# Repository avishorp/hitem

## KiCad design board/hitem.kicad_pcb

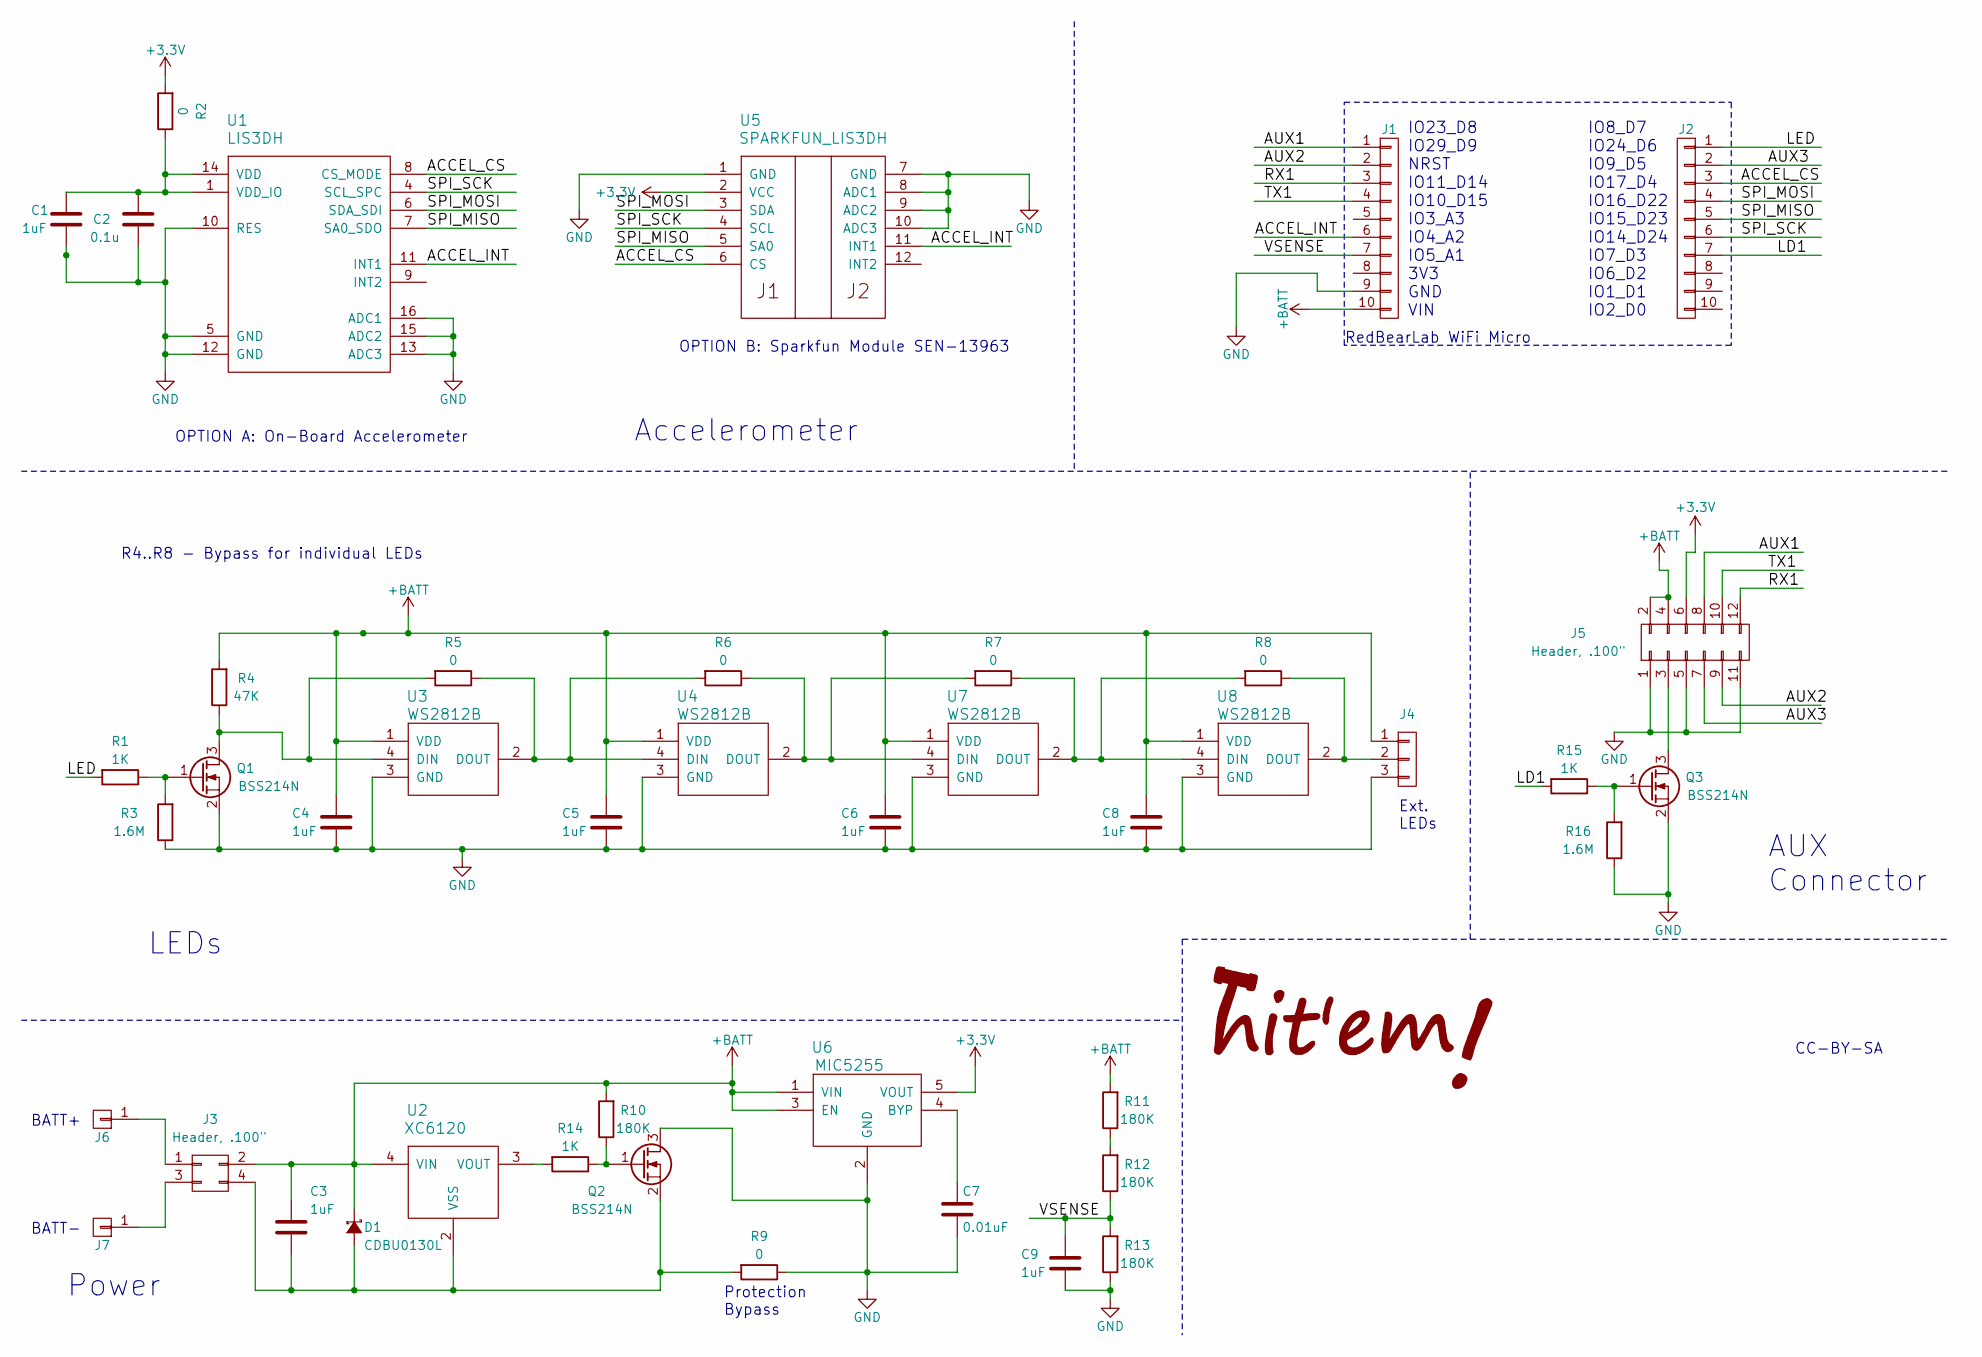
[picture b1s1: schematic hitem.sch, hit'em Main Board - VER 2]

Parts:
C1, C3, C4, C5, C6, C8, C9: 1uF; R0603
C2: 0.1u; R0603
C7: 0.01uF; R0603
D1: CDBU0130L; SOD-523F; mouser 750-CDBU0130R-HF
J1, J2: Female, 0.1\", 1x10; Pin_Header_Straight_1x10
J3: Header, .100\"; Pin_Header_Straight_2x02
J4: CONN_01X03; SMT_HOOKUP_3
J5: Header, .100\"; Pin_Header_Straight_2x06
J6, J7: CONN_01X01; BATTERY_CONTACT
Q1, Q2, Q3: BSS214N; SOT-23; mouser 726-BSS214NH6327XT
R1, R14, R15: 1K; R0603
R2, R5, R6, R7, R8, R9: 0; R0603
R3, R16: 1.6M; R0603
R4: 47K; R0603
R10, R11, R12, R13: 180K; R0603
U1: LIS3DH
U2: XC6120; SSOT-24
U3, U4, U7, U8: WS2812B; WS2812
U5: SPARKFUN_LIS3DH; SEN-13963
U6: MIC5255

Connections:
+3V3: J5.6, R2.2, U5.2 (VCC), U6.5 (VOUT)
+BATT: C3.1, C4.1, C5.1, C6.1, C8.1, D1.1 (K), J1.10, J3.2, J4.1, J5.2, J5.4, R4.2, R10.2, R11.2, U2.4 (VIN), U3.1 (VDD), U4.1 (VDD), U6.1 (VIN), U6.3 (EN), U7.1 (VDD), U8.1 (VDD)
/ACCEL_CS: J2.3, U1.8 (CS_MODE), U5.6 (CS)
/ACCEL_INT: J1.6, U1.11 (INT1), U5.11 (INT1)
/AUX1: J1.1, J5.8
/AUX2: J1.2, J5.9
/AUX3: J2.2, J5.7
/LD1: J2.7, R15.2
/LED: J2.1, R1.2
/RX1: J1.3, J5.12
/SPI_MISO: J2.5, U1.7 (SA0_SDO), U5.5 (SA0)
/SPI_MOSI: J2.4, U1.6 (SDA_SDI), U5.3 (SDA)
/SPI_SCK: J2.6, U1.4 (SCL_SPC), U5.4 (SCL)
/TX1: J1.4, J5.10
/VSENSE: C9.1, J1.7, R12.1, R13.2
GND: C1.2, C2.2, C4.2, C5.2, C6.2, C7.2, C8.2, C9.2, J1.9, J4.3, J5.1, J5.5, J5.11, Q1.2 (S), Q2.3 (D), Q3.2 (S), R3.1, R9.1, R13.1, R16.1, U1.5 (GND), U1.10 (RES), U1.12 (GND), U1.13 (ADC3), U1.15 (ADC2), U1.16 (ADC1), U3.3 (GND), U4.3 (GND), U5.1 (GND), U5.7 (GND), U5.8 (ADC1), U5.9 (ADC2), U5.10 (ADC3), U6.2 (GND), U7.3 (GND), U8.3 (GND)
unnamed: C1.1, C2.1, R2.1, U1.1 (VDD_IO), U1.14 (VDD)
unnamed: C3.2, D1.2 (A), J3.4, Q2.2 (S), R9.2, U2.2 (VSS)
unnamed: C7.1, U6.4 (BYP)
unnamed: J3.3, J7.1
unnamed: J4.2, R8.1, U8.2 (DOUT)
unnamed: J5.3, Q3.3 (D)
unnamed: Q1.1 (G), R1.1, R3.2
unnamed: Q1.3 (D), R4.1, R5.2, U3.4 (DIN)
unnamed: Q2.1 (G), R10.1, R14.1
unnamed: Q3.1 (G), R15.1, R16.2
unnamed: R5.1, R6.2, U3.2 (DOUT), U4.4 (DIN)
unnamed: R6.1, R7.2, U4.2 (DOUT), U7.4 (DIN)
unnamed: R7.1, R8.2, U7.2 (DOUT), U8.4 (DIN)
unnamed: R11.1, R12.2
unnamed: R14.2, U2.3 (VOUT)

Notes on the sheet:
Accelerometer
IO23_D8 IO29_D9 NRST IO11_D14 IO10_D15 IO3_A3 IO4_A2 IO5_A1 3V3 GND VIN
IO8_D7 IO24_D6 IO9_D5 IO17_D4 IO16_D22 IO15_D23 IO14_D24 IO7_D3 IO6_D2 IO1_D1 IO2_D0
RedBearLab WiFi Micro
BATT+
BATT-
OPTION A: On-Board Accelerometer
OPTION B: Sparkfun Module SEN-13963
Protection Bypass
AUX Connector
LEDs
Power
R4..R8 - Bypass for individual LEDs
Ext. LEDs
CC-BY-SA

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
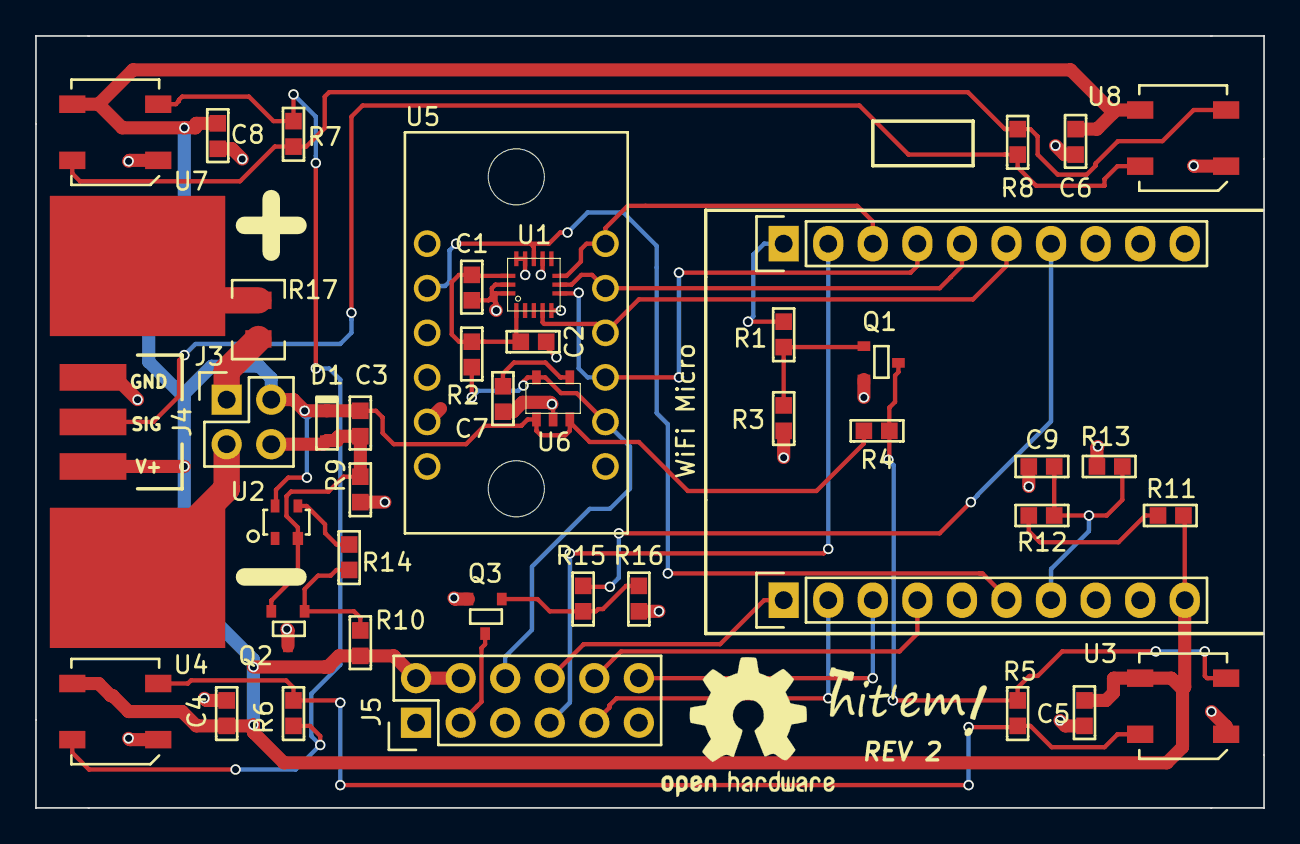
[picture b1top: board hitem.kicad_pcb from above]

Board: 2 copper layers, 70.0 x 44.0 mm, 45 parts (0 on the bottom side), 33 nets.

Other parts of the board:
R17: PTC, 1.5A; BEL-0ZCK

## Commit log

2016-02-13 Initial board design (with PIC & nRF)
2016-02-16 Change the design to be based on RedBearLab WiFi Micro
2016-02-29 Final version of schematic & PCB
2016-03-17 Initial firmware - LED test
2016-03-17 Add logo graphics files
2016-03-29 Move the test firmware to the software subtree
2016-03-29 Add basic CCS project
2016-03-30 Add LED control module
2016-03-30 Fixed timer initialization issue, causing LEDs not to work correctly
2016-03-30 SimpleLink initialization
2016-03-31 Add configuration module (stub)
2016-03-31 Add mainloop infrastructure
2016-04-03 Connection success, socket creation
2016-04-03 Send discovery request message
2016-04-03 Add initial server with discovery capability
2016-04-03 Add discovery packet reception capability
2016-04-04 Add timing module
2016-04-04 Add support for LED patterns
2016-04-04 Assign LED patterns for connect WLAN and connect server events
2016-04-05 Add main file
2016-04-05 Add EP server connection and protocol parsing
2016-04-05 Add "packed" attribute to the message array
2016-04-05 Implement re-connection to the EP server in case of disconnection
2016-04-05 Add initial EP server implementation
2016-04-05 Add WELCOME message parsing
2016-04-05 Move the protocol parser into a module of its own
2016-04-06 Add child loggers
2016-04-06 WLAN disconnect handling & protocol parsing bugfix
2016-04-06 Implement command sending to the endpoint
2016-04-06 Implement sync request and response
2016-04-06 Implement SYNC requset & response over TCP
2016-04-06 Start working on the EPManager object, partial code
2016-04-07 Move hit detection (ADC) to a different file; Create the discovery port dynamically
2016-04-07 Enter sleep mode
2016-04-08 Replace sleep mode with hibernate
2016-04-09 Sleep after fatal error
2016-04-09 Change the Piezo ADC channel to 2, to align with the wake-up pin
2016-04-09 Read configuration from a file, add script to create configuration files
2016-04-09 Turn off ADC before going to sleep
2016-04-09 Make the chirp pattern repetitive
2016-04-09 Add HIT message parsing
2016-04-09 Changed EPServer to EPManager object
2016-04-09 Implement & enable UDP sync
2016-04-09 Add battery level message parsing
2016-04-10 Final endpoint configuration file
2016-04-10 Initial Electron application
2016-04-10 Set up react + webpack
2016-04-10 Main screen layout
2016-04-10 State and component structuring
2016-04-11 Implement unit manager
2016-04-11 Handle unit-by-unit hit
2016-04-11 Testing IPC
2016-04-12 Change the start script to launch the GUI
2016-04-12 Start EPServer and connect to it
2016-04-12 Initial implementation of join screen
2016-04-12 Protect against hammer re-assignment
2016-04-12 Try to load the app directly with babel (without webpack)
2016-04-12 Add text message and ready logic
2016-04-12 Add background and style main screen
2016-04-12 Add start key, countdown & logging
2016-04-12 Add initial score
2016-04-13 setColor implemented
2016-04-13 Add hat colors, color change detection in EP component
2016-04-13 Fix bug in EP change detection algorithm
2016-04-13 Fix incorrect same personality hit event emission
2016-04-13 Move hat color state into slots, add startGame action
2016-04-13 Add game color transition
2016-04-13 Implement basic game logic
2016-04-13 Restructure slot state
2016-04-13 Fix color assignment bug
2016-04-13 Add game over graphics
2016-04-14 Unconditional periodic refesh of endpoints
2016-04-14 Always assume one-message-at-a-time reception
2016-04-14 Fix color shuffle, add final states
2016-04-14 Implement reset
2016-04-14 Programmatic emulation of hits
2016-04-14 Add successful/unsuccessful hit indication
2016-04-14 Change the message display font
2016-04-14 Fix event emulation sequencing
2016-04-14 Make sure that hammers that are already joined are not joining again
2016-04-14 Poor man's deathmatch
2016-04-14 Fix flickering due to border width
2016-04-14 Fix font size and add "winner" message
2016-04-14 Fix winner detection logic
2016-07-05 Fix typing problems in the state machine scheme, get rid of the state table and fix a bunch of other minor warnings
2016-07-06 Add script for creating trivial file packages
2016-07-06 Add magic number to the beginning of the package file
2016-07-06 Separate the state definition into a separate file
2016-07-06 Missing file
2016-07-07 Add firmware version number & filename to the discrovery response
2016-07-13 Add version functions
2016-07-13 Add TFTP server to the discovery module
2016-07-14 Implement extended discovery handshake
2016-07-14 Add board tracking option
2016-07-19 Add TI TFTP client code
2016-07-19 Add test command to the npm package
2016-07-19 Allow TFTP port custumization and test TFTP
2016-07-20 Add TFTP port to the discovery response
2016-07-24 Move OTA functionality to a standalone file
2016-07-25 Create OTA metadata and serve it through TFTP
2016-07-25 OTA Metadata read and parsed by the client
2016-07-26 Add TFTP direct download capability, fetch OTA files
2016-07-27 Allow destination filename specification in the firmware metadata file
2016-07-29 Add MD5 Checksum calc & verify
2016-07-31 OTA version check & reset after successful update
2016-07-31 Warning cleanup
2016-08-01 Change the LED flashing pattern while searching connection to conserve energy
2016-09-07 Configuration changes
2016-09-07 Split the unit ID/WLAN credentials to two separate files.
2016-09-07 Remove old unnecessary file
2016-09-07 Rewrite hit detection mechanism
2016-09-07 Fix advertising of TFTP port through discovery response
2016-09-07 Add firmware version 0.0.6 to OTA
2016-09-11 Add UDP console facility
2016-09-11 Dump raw ADC valuse to a UDP socket
2016-09-12 Adjust hit detect threshold
2016-09-12 Add option to disable OTA TFTP server
2016-09-12 Improve hit logging message
2016-09-13 Add UDP sync request option to the server
2016-09-13 Add firmware version 0.0.7 to OTA
2016-09-20 Change the firmware version (only version, not content) to 2.0.7
2016-09-22 Implement battery level measurment
2016-09-22 Add source IP printing to the UDP log dumper
2016-09-22 Apply UDP sync to the hit detection mechanism
2016-09-22 Extend the TCP message prolog to eliminate false parsing
2016-09-22 Initial extended endpoint tester
2016-09-25 Fixes to the setColor mechanism (both server and endpoint)
2016-09-25 Unify indication & color setting under the same function, and make all indications repetitive
2016-09-26 Add keepalive message and handle unit removal correctly
2016-09-29 Battery low/critical detection and handling
2016-09-30 Firmware version 2.1.0
2016-10-06 Replace webpack with electron-compile
2016-10-07 Trying to get this to work with electron-compile, but without success
2016-10-09 Initial transition to MobX
2016-10-10 Emulation infrastructure
2016-10-10 Join logic & emulation
2016-10-11 Initial start game & countdown logic
2016-10-13 Countdown graphics
2016-10-13 Initial color shuffling, hat color visualisation
2016-10-14 Add some more game logic
2016-10-14 Add comment support for the JSON config file
2016-10-14 Start up the discovery service properly
2016-10-17 Add SetThreshold command
2016-10-17 Remove cyclic "Now is ..." report (used for debugging)
2016-10-17 Add firmware version 2.2.0
2016-10-18 Fix UDP sync mechanism
2016-10-19 Fix server port assignment bug
2016-10-19 Disable UDP debug prints - causing software stuck
2016-10-19 Add an option to disable low battery detection
2016-10-19 Print the FW version properly
2016-10-19 Firmware version 2.2.1
2016-10-20 Add per-unit hit threshold calibration
2016-10-20 Add actual calibration data
2016-10-20 Implement actual endpoint communication
2016-10-20 Check that hammers and hats are not re-assigned
2016-10-21 Deathmatch screen styling
2016-10-21 Implement deathmatch logic
2016-10-21 Add fireworks effect (now working yet)
2016-10-24 Add direct analog sample access debug mode
2016-10-24 Change the polarity of the hit threshold detection
2017-01-02 Add SPI pins to pinmux
2017-02-06 Schematic for rev B
2017-02-07 Code for reading from LIS3DSH accelerometer
2017-02-11 Finish schematic & board layout (without routing)
2017-02-14 Finish PCB of REV. 2
2017-02-14 Add "VER 2" to the schematic title block
2017-02-15 Fix incorrect footprint for U2
2017-02-16 Add protection Polyfuse
2017-06-26 Initial code for writing to WS2812B LEDs
2017-06-26 Update the LED module to work with indexed colors
2017-06-26 Disable battery monitoring for debugging
2017-06-26 Add support for LIS3DH accelerometer

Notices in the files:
board/hitem.sch:
https://creativecommons.org/licenses/by-sa/4.0
Released under Creative Commons
